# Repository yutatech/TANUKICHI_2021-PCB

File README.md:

# TANUKICHI_2021-PCB
This PCB is developed for RoboCup Junior Soccer. The robot has competed as "CAIO Tezukayama" in 2019 and "Leopard" in 2021.

## Related Web sites
- [Yuta's Blog](http://yuta.techblog.jp)
- [ Yuta - YouTube Channel](https://www.youtube.com/@yuta9428)
- [ Yuta@ciao_yuta - Twitter](https://twitter.com/ciao_yuta)

## Related Repositories
- [yutatech/RoboCup2021](https://github.com/yutatech/RoboCup2021)
- [yutatech/TANUKICHI_2021-Software](https://github.com/yutatech/TANUKICHI_2021-Software)

## Related Resources
#### TDP
- [Leopard RoboCup 2021 Team Discription Paper](http://yuta.techblog.jp/RoboCupJapanTournament2021/Leopard%20RoboCup%202021%20Team%20Discription%20Paper.pdf)

#### Video
- [Video - Leopard (Soccer Open) - RoboCup 2021 WORLDWIDE](https://www.youtube.com/watch?v=Lgoi_pQrCUY)
	- [This video](https://www.youtube.com/watch?v=PFkYVE7N84A) and [this video](https://www.youtube.com/watch?v=1l03lD6fXiQ) are also the same. Uploaded from TokyoTech.

## Awards
- ロボカップジュニア日本大会2021オンライン (RoboCup Junior Japan Tournament 2021 Online)
	- サッカーオープン 優勝 (SoccerOpen 1st Place)
	- ベストプレゼンビデオ賞 (Best Presentation Video Award)
	- ベストインタビュー賞 (Best Interview Award)
	- ベストビジュアルポスター賞 (Best Visual Poster Award)
- RoboCup 2021 WORLDWIDE
	- SoccerOpen Indvidual 1st Place
	- SoccerOpen SuperTeam 1st Place

## Environment
These files are edited with KiCAD 5.1.5

## PCB design files
- MAIN
	- This PCB is the main board of the robot. 
- MOTOR
	- This PCB drives 4 motors and 2 kickers. It is connected to MAIN with pin headers.
- LINE
	- This PCB includes 2 types of line sensor boards. The robot has two sensor boards of each type.
- TOP
	- This PCB distributes the wiring from MAIN to the devices mounted on top of the robot.
- BOTTOM
	- This PCB is connected to the line sensor board without using cables.
- BOOST V1
	- This PCB is a boost circuit for kickers. It outputs 60V. This version is installed to the robot because it is stable and works well.
- BOOST V2
	- This PCB is also a boost circuit for kickers. It outputs 150V. This version is an improvement on V1, but was not adopted because it would have caused noise in the surrounding circuit.
- ENCODER
	- This PCB is a magnetic pulse encoder board.
- PROTECTION
	- This PCB is Li-PO Battery protection circuit. The voltage of each cell is not monitored, so any imitation should be done at your own risk.

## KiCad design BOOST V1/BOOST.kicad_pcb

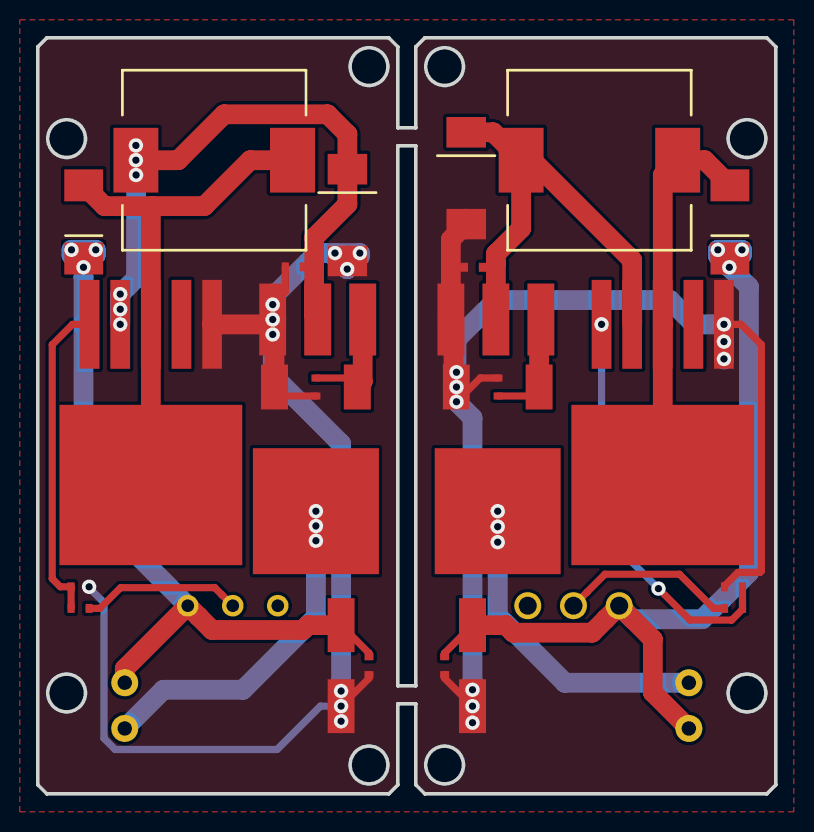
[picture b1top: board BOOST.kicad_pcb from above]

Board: 2 copper layers, 41.0 x 42.0 mm, 28 parts (0 on the bottom side), 15 nets.

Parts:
C1, C4: 100u; TANTALCAP-6032
C2, C3, C5, C6: 100n; 1005
D1, D2: D_Small; DO-214AC
J1, J4: INPUT; 3Pads
J2, J5: CAPACITOR; 2Pads
J3, J6: SOLENOID; Molex_2pin_angled
L1, L2: L; Inductor_10x10x3.8
Q1, Q2: Q_NMOS_GDS; TO-252
R1, R4: 2K; 1005
R2, R5: 470R; 1005
R3, R6: 1K; 1005
RV1, RV2: 20K; CONN_01x03
XL1, XL2: XL6019; TO263-5L

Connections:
GND: C1.2, C2.2, C3.2, C4.2, C5.2, C6.2, J1.1, J2.2, J4.1, J5.2, Q1.3, Q2.3, R2.2, R3.1, R5.2, R6.1, XL1.1, XL2.1
unnamed: C1.1, C2.1, J1.2, L1.2, XL1.4
unnamed: C3.1, D1.1, J2.1, J3.1, RV1.1
unnamed: C4.1, C5.1, J4.2, L2.2, XL2.4
unnamed: C6.1, D2.1, J5.1, J6.1, RV2.1
unnamed: D1.2, L1.1, XL1.3
unnamed: D2.2, L2.1, XL2.3
unnamed: J1.3, Q1.1, R3.2
unnamed: J3.2, Q1.2
unnamed: J4.3, Q2.1, R6.2
unnamed: J6.2, Q2.2
unnamed: R1.1, RV1.2
unnamed: R1.2, R2.1, XL1.5
unnamed: R4.1, RV2.2
unnamed: R4.2, R5.1, XL2.5

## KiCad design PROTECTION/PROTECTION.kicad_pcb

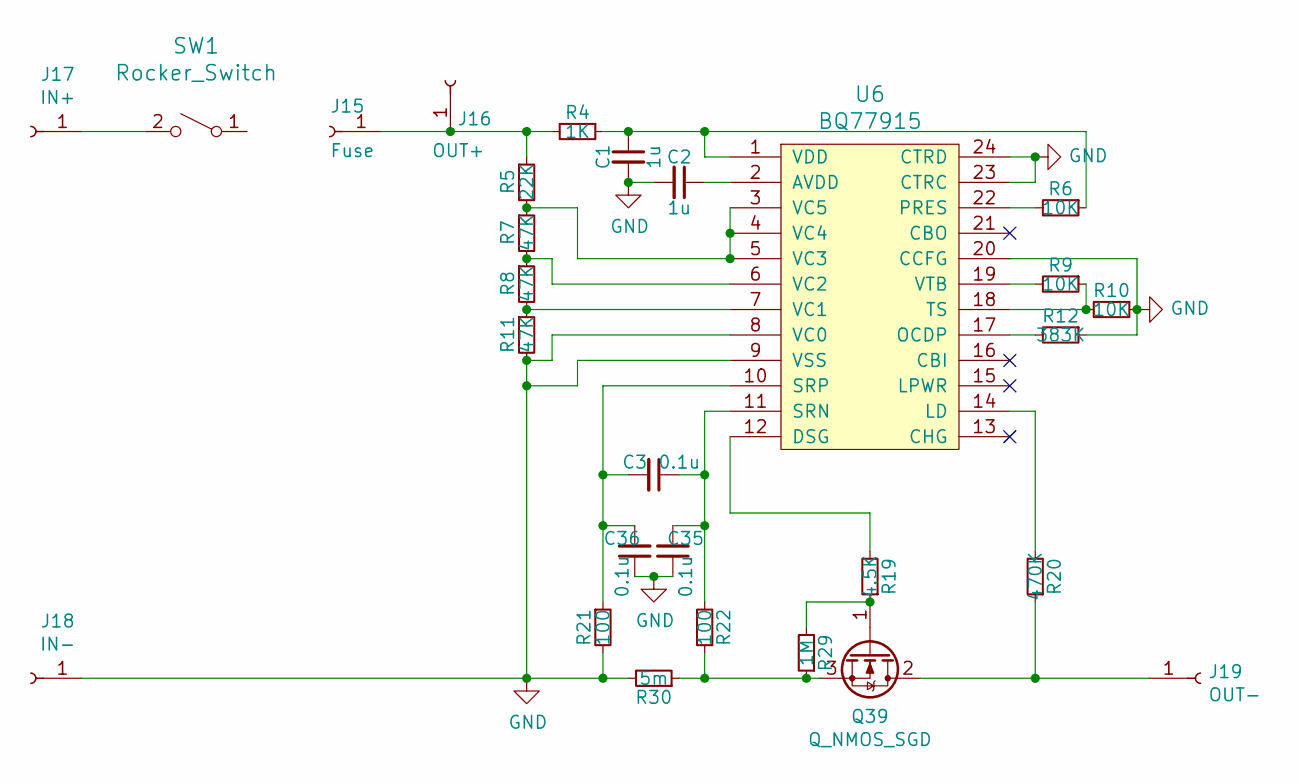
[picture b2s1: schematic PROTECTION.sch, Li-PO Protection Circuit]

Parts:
C1, C2: 1u; 1005
C3, C35, C36: 0.1u; 1005
J15: Fuse; 1PIN
J16: OUT+; 1PIN
J17: IN+; 1PIN
J18: IN-; 1PIN
J19: OUT-; 1PIN
Q39: Q_NMOS_SGD; TO-252; Part # DMTH6005LK3-13
R4: 1K; 1005
R5: 22K; 1005
R6, R9, R10: 10K; 1005
R7, R8, R11: 47K; 1005
R12: 383K; 1005
R19: 4.5K; 1005
R20: 470K; 1005
R21, R22: 100; 1005
R29: 1M; 1005
R30: 5m; 6432; Part # PCS2512FR0050ET
SW1: Rocker_Switch; 2Pads; Part # DS-850K-S-LG-K
U6: BQ77915; TSSOP-24

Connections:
GND: C1.2, C2.2, C35.1, C36.1, J18.1, R10.1, R11.2, R12.1, R21.2, R30.2, U6.8 (VC0), U6.9 (VSS), U6.20 (CCFG), U6.23 (CTRC), U6.24 (CTRD)
unnamed: C1.1, R4.1, R6.1, U6.1 (VDD)
unnamed: C2.1, U6.2 (AVDD)
unnamed: C3.1, C35.2, R22.2, U6.11 (SRN)
unnamed: C3.2, C36.2, R21.1, U6.10 (SRP)
unnamed: J15.1, J16.1, R4.2, R5.1
unnamed: J17.1, SW1.2 (B)
unnamed: J19.1, Q39.2 (D), R20.1
unnamed: Q39.1 (G), R19.1, R29.2
unnamed: Q39.3 (S), R22.1, R29.1, R30.1
unnamed: R5.2, R7.1, U6.3 (VC5), U6.4 (VC4), U6.5 (VC3)
unnamed: R6.2, U6.22 (PRES)
unnamed: R7.2, R8.1, U6.6 (VC2)
unnamed: R9.2, U6.19 (VTB)
unnamed: R9.1, R10.2, U6.18 (TS)
unnamed: R8.2, R11.1, U6.7 (VC1)
unnamed: R12.2, U6.17 (OCDP)
unnamed: R19.2, U6.12 (DSG)
unnamed: R20.2, U6.14 (LD)

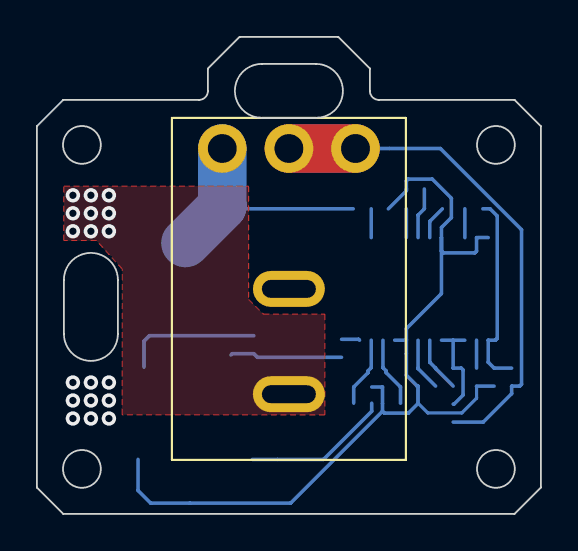
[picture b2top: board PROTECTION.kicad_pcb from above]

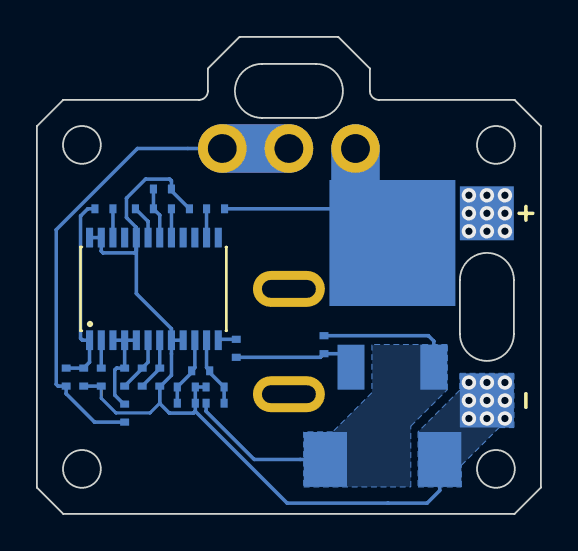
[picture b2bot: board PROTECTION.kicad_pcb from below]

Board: 2 copper layers, 28.0 x 26.5 mm, 28 parts (24 on the bottom side), 19 nets.

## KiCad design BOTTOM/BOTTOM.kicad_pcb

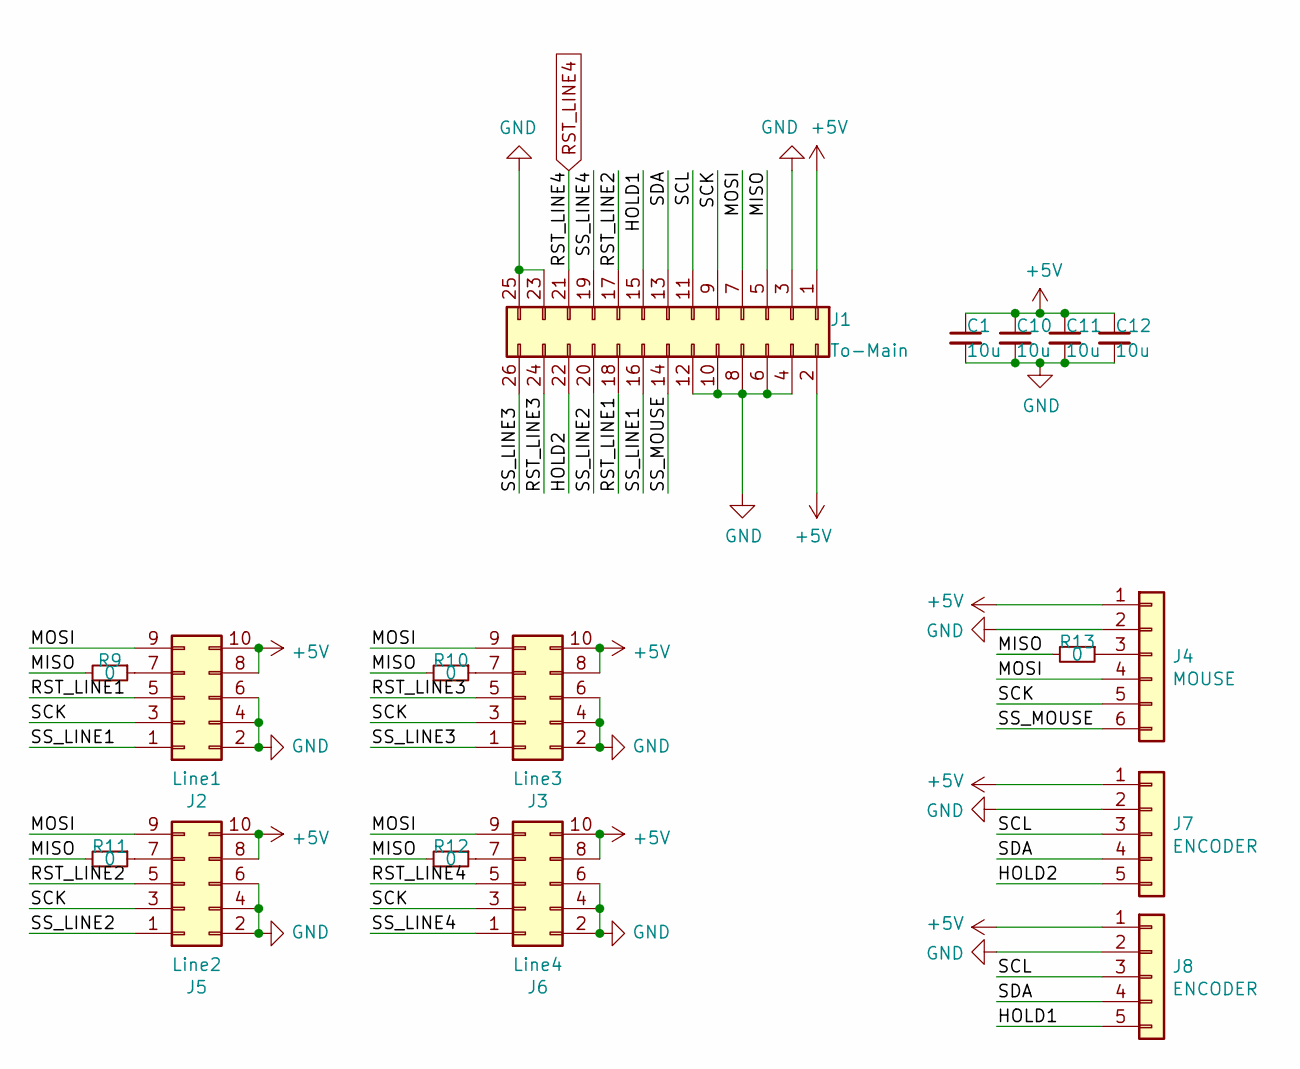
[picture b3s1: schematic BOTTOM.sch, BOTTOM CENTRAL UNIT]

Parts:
C1, C10, C11, C12: 10u; 2012
J1: To-Main; IDC_Header_Straight_26pins_P1.27mm; Part # 3220-26-0100-00
J2: Line1; CONN_SPRING_02x05_PADS
J3: Line3; CONN_SPRING_02x05_PADS
J4: MOUSE; CONN_01x06
J5: Line2; CONN_SPRING_02x05_PADS
J6: Line4; CONN_SPRING_02x05_PADS
J7, J8: ENCODER; CONN_01x05
R9, R10, R11, R12, R13: 0; 1005

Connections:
+5V: C1.1, C10.1, C11.1, C12.1, J1.1, J1.2, J2.8, J2.10, J3.8, J3.10, J4.1, J5.8, J5.10, J6.8, J6.10, J7.1, J8.1
/HOLD1: J1.15, J8.5
/HOLD2: J1.22, J7.5
/MISO: J1.5, R9.2, R10.2, R11.2, R12.2, R13.2
/MOSI: J1.7, J2.9, J3.9, J4.4, J5.9, J6.9
/RST_LINE1: J1.18, J2.5
/RST_LINE2: J1.17, J5.5
/RST_LINE3: J1.24, J3.5
/SCK: J1.9, J2.3, J3.3, J4.5, J5.3, J6.3
/SCL: J1.11, J7.3, J8.3
/SDA: J1.13, J7.4, J8.4
/SS_LINE1: J1.16, J2.1
/SS_LINE2: J1.20, J5.1
/SS_LINE3: J1.26, J3.1
/SS_LINE4: J1.19, J6.1
/SS_MOUSE: J1.14, J4.6
GND: C1.2, C10.2, C11.2, C12.2, J1.3, J1.4, J1.6, J1.8, J1.10, J1.12, J1.23, J1.25, J2.2, J2.4, J2.6, J3.2, J3.4, J3.6, J4.2, J5.2, J5.4, J5.6, J6.2, J6.4, J6.6, J7.2, J8.2
unnamed: J2.7, R9.1
unnamed: J3.7, R10.1
unnamed: J4.3, R13.1
unnamed: J5.7, R11.1
unnamed: J6.7, R12.1
RST_LINE4: J1.21, J6.5

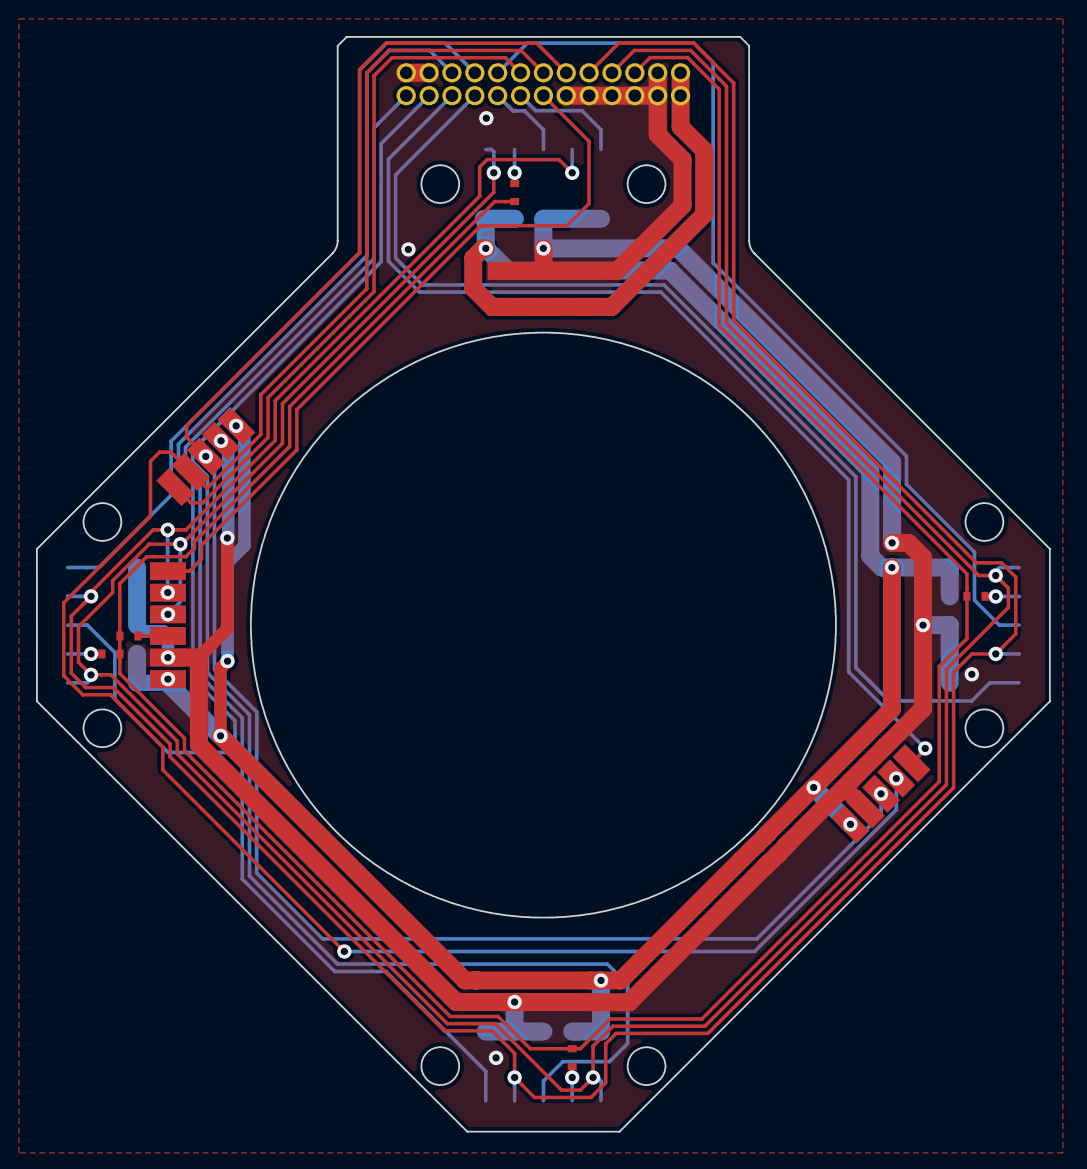
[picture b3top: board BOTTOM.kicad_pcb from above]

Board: 2 copper layers, 56.3 x 60.8 mm, 17 parts (0 on the bottom side), 23 nets.

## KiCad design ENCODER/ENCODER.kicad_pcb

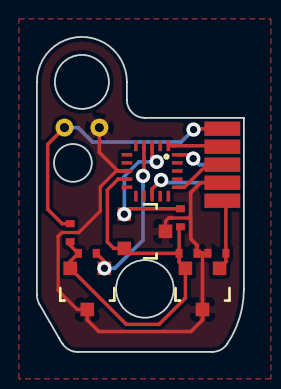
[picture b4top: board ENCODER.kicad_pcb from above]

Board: 2 copper layers, 11.5 x 17.5 mm, 12 parts (1 on the bottom side), 10 nets.

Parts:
C32, C33: 1u; 1005
J5: Conn_01x05; CONN_01x05
J11: Conn_01x02; 2Pads
Q24: Q_Photo_NPN; 2Pads
R28: 4.7K; 1005
R29, R30: 10K; 1005
U11: AP7333; Q_SOT-23
U12, U13: AH1751; Q_SOT-23
U14: ATtiny84A-MMH; QFN-20_P0.45

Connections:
+3V3: C33.2, R28.2, R29.1, R30.1, U11.2, U12.2, U13.2, U14.9
+5V: C32.1, J5.5, U11.1
/HOLD: J5.1, Q24.1, R28.1
/MISO: J11.2, U14.20
/RESET: J11.1, U14.13
/SCL\SCK: J5.2, U14.1
/SDA\MOSI: J5.3, U14.16
GND: C32.2, C33.1, J5.4, Q24.2, U11.3, U12.3, U13.3, U14.8
unnamed: R29.2, U12.1, U14.4
unnamed: R30.2, U13.1, U14.3

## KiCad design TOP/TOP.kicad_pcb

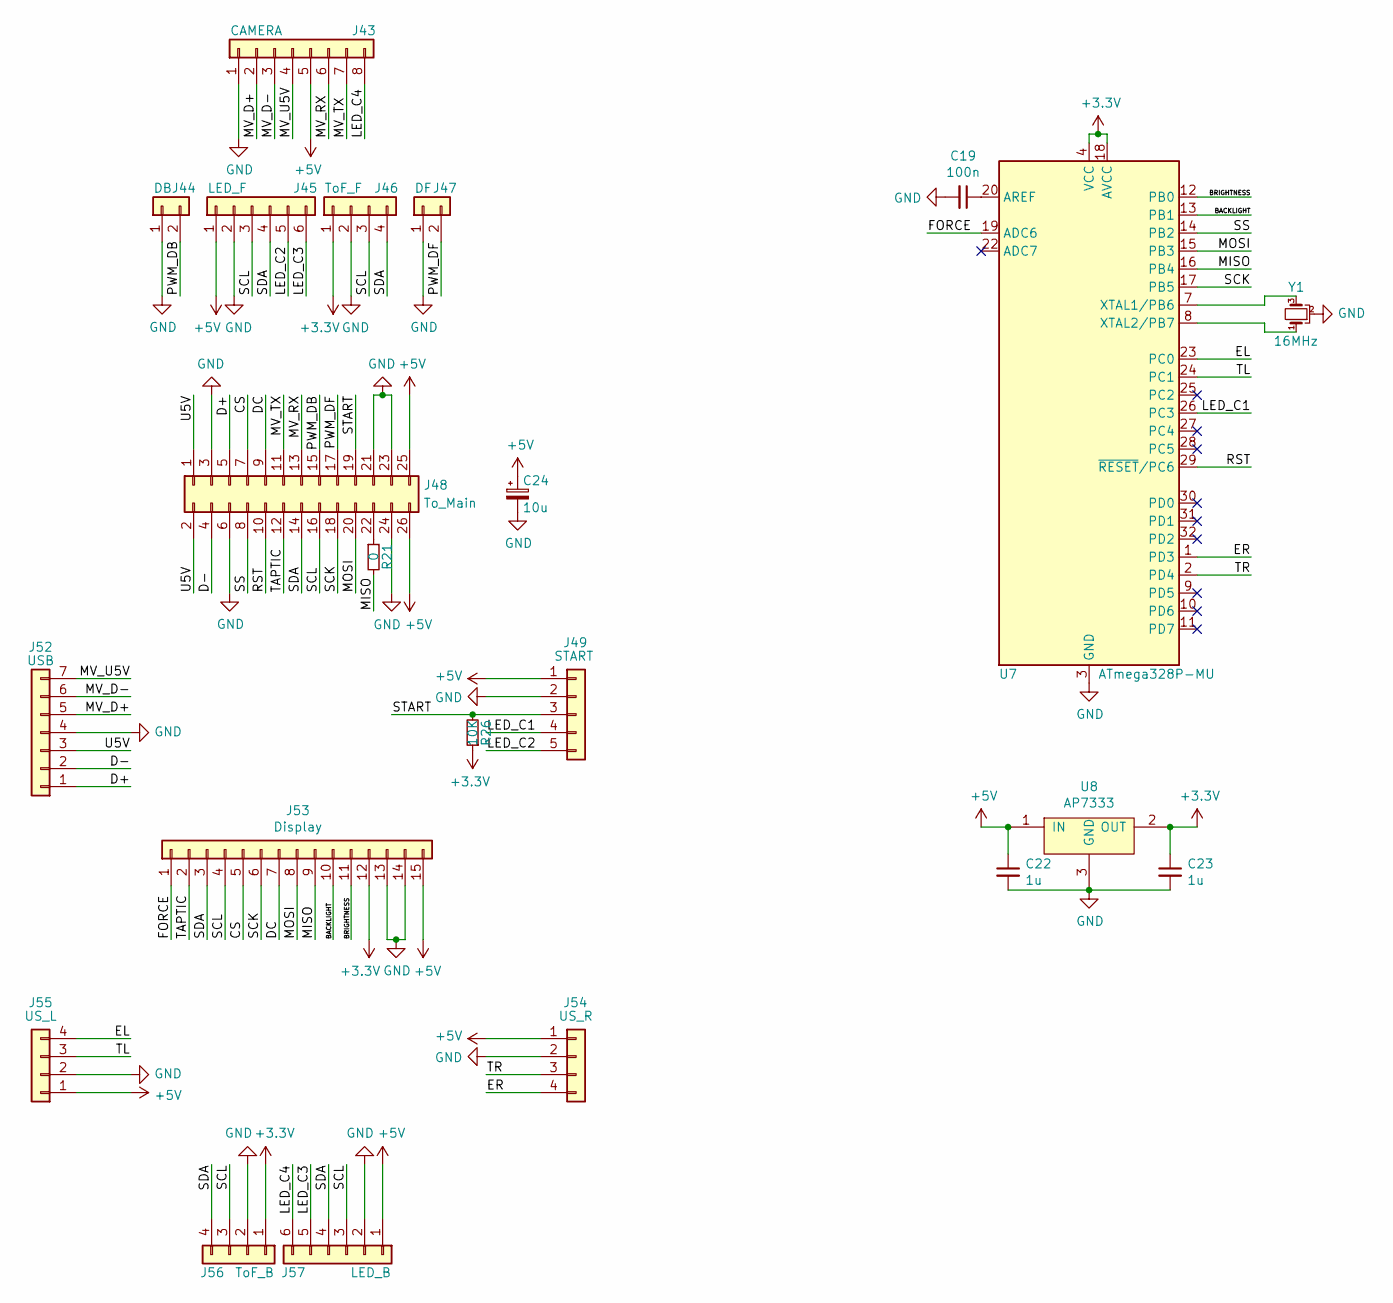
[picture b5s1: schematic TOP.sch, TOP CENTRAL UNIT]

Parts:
C19: 100n; 1005
C22, C23: 1u; 1005
C24: 10u; CAPACITOR_φ4
J43: CAMERA; PH-ST08
J44: DB; PH-ST02
J45: LED_F; PH-ST06
J46: ToF_F; PH-ST04
J47: DF; PH-ST02
J48: To_Main; IDC_Header_Straight_26pins_P1.27mm; Part # 3220-26-0100-00
J49: START; PH-ST05
J52: USB; PH-ST07
J53: Display; FFC 15P
J54: US_R; PH-ST04
J55: US_L; PH-ST04
J56: ToF_B; PH-ST04
J57: LED_B; PH-ST06
R21: 0; 1005
R26: 10K; 1005
U7: ATmega328P-MU; VQFN-32-5x5mm_P0.5mm
U8: AP7333; Q_SOT-23
Y1: 16MHz; CERALOCK; Part # CSTNE16M0V530000R0

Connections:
+3V3: C23.1, J46.1, J53.12, J56.1, R26.1, U7.4 (VCC), U7.6 (VCC), U7.18 (AVCC), U8.2 (OUT)
+5V: C22.1, C24.1, J43.5, J45.1, J48.25, J48.26, J49.1, J53.15, J54.1, J55.1, J57.1, U8.1 (IN)
/BACKLIGHT: J53.10, U7.13 (PB1)
/BRIGHTNESS: J53.11, U7.12 (PB0)
/CS: J48.7, J53.5
/D+: J48.5, J52.1
/D-: J48.4, J52.2
/DC: J48.9, J53.7
/EL: J55.4, U7.23 (PC0)
/ER: J54.4, U7.1 (PD3)
/FORCE: J53.1, U7.19 (ADC6)
/LED_C1: J49.4, U7.26 (PC3)
/LED_C2: J45.5, J49.5
/LED_C3: J45.6, J57.5
/LED_C4: J43.8, J57.6
/MISO: J53.9, R21.2, U7.16 (PB4)
/MOSI: J48.20, J53.8, U7.15 (PB3)
/MV_D+: J43.2, J52.5
/MV_D-: J43.3, J52.6
/MV_RX: J43.6, J48.13
/MV_TX: J43.7, J48.11
/MV_U5V: J43.4, J52.7
/PWM_DB: J44.2, J48.15
/PWM_DF: J47.2, J48.17
/RST: J48.10, U7.29 (~RESET~/PC6)
/SCK: J48.18, J53.6, U7.17 (PB5)
/SCL: J45.3, J46.3, J48.16, J53.4, J56.3, J57.3
/SDA: J45.4, J46.4, J48.14, J53.3, J56.4, J57.4
/SS: J48.8, U7.14 (PB2)
/START: J48.19, J49.3, R26.2
/TAPTIC: J48.12, J53.2
/TL: J55.3, U7.24 (PC1)
/TR: J54.3, U7.2 (PD4)
/U5V: J48.1, J48.2, J52.3
GND: C19.2, C22.2, C23.2, C24.2, J43.1, J44.1, J45.2, J46.2, J47.1, J48.3, J48.6, J48.21, J48.23, J48.24, J49.2, J52.4, J53.13, J53.14, J54.2, J55.2, J56.2, J57.2, U7.3 (GND), U7.5 (GND), U7.21 (GND), U7.33 (GND), U8.3 (GND), Y1.2
unnamed: C19.1, U7.20 (AREF)
unnamed: J48.22, R21.1
unnamed: U7.7 (XTAL1/PB6), Y1.3
unnamed: U7.8 (XTAL2/PB7), Y1.1

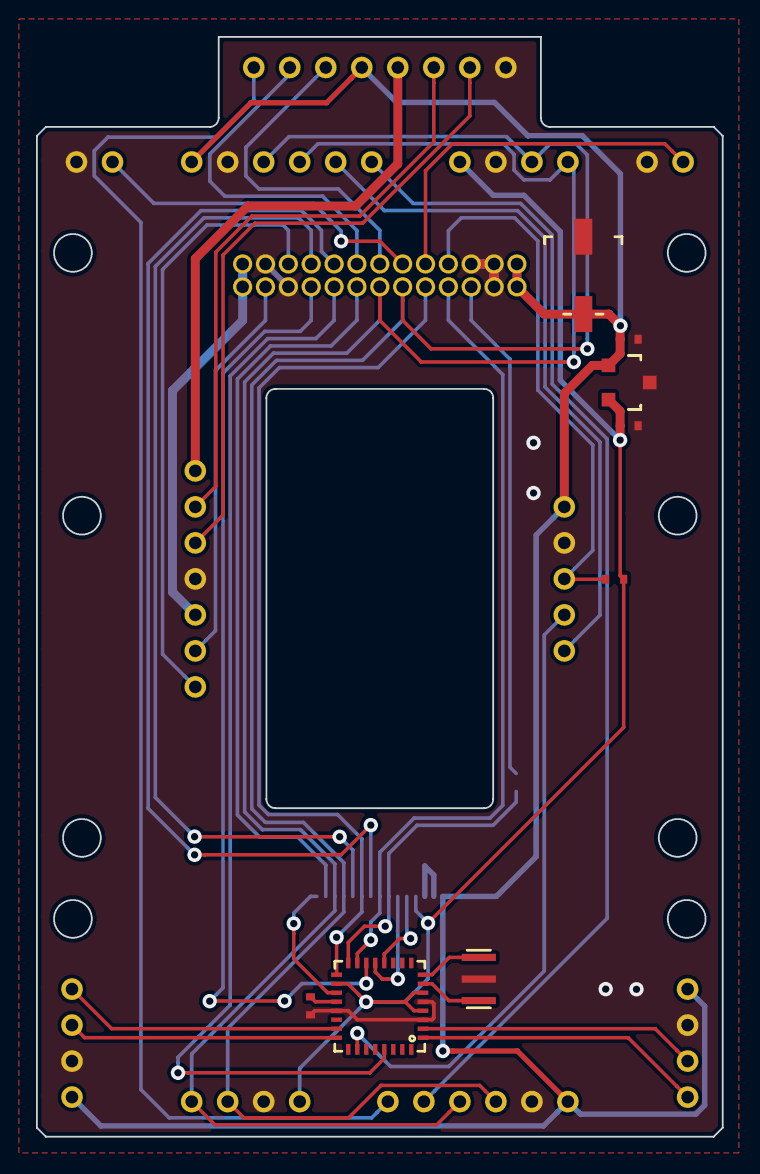
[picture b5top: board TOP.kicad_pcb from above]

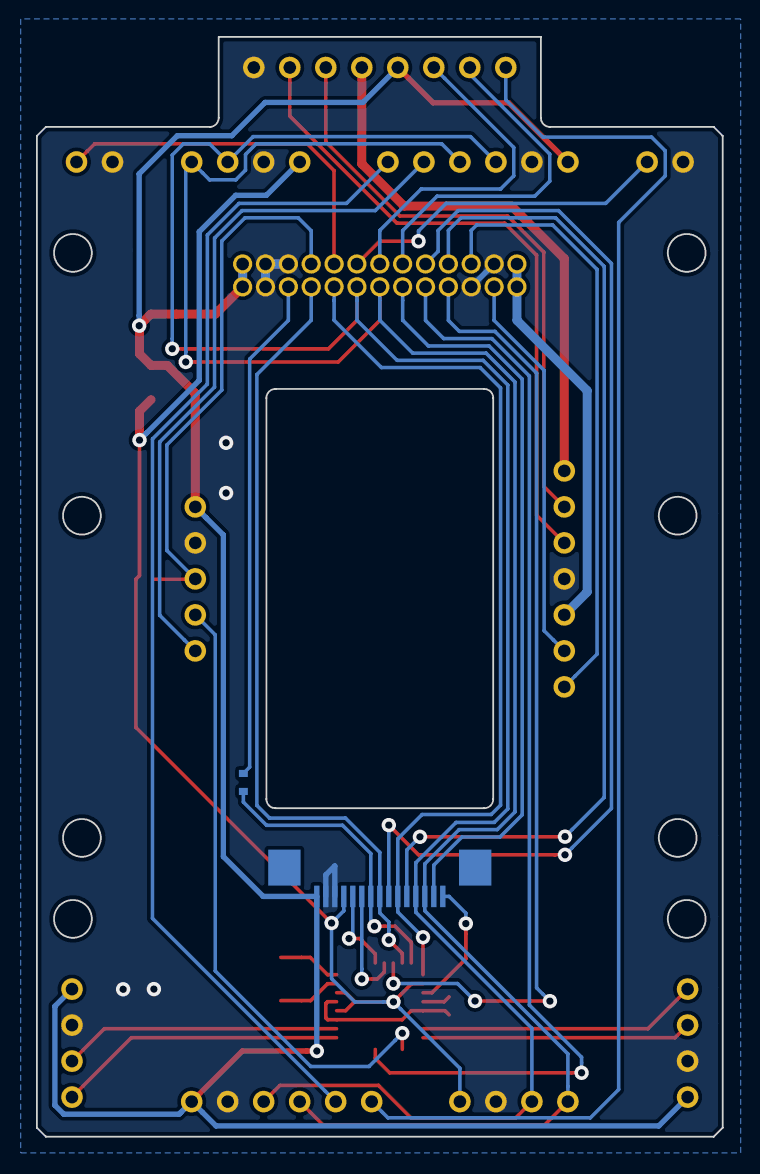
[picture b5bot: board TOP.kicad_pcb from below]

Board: 2 copper layers, 38.1 x 61.1 mm, 22 parts (13 on the bottom side), 39 nets.

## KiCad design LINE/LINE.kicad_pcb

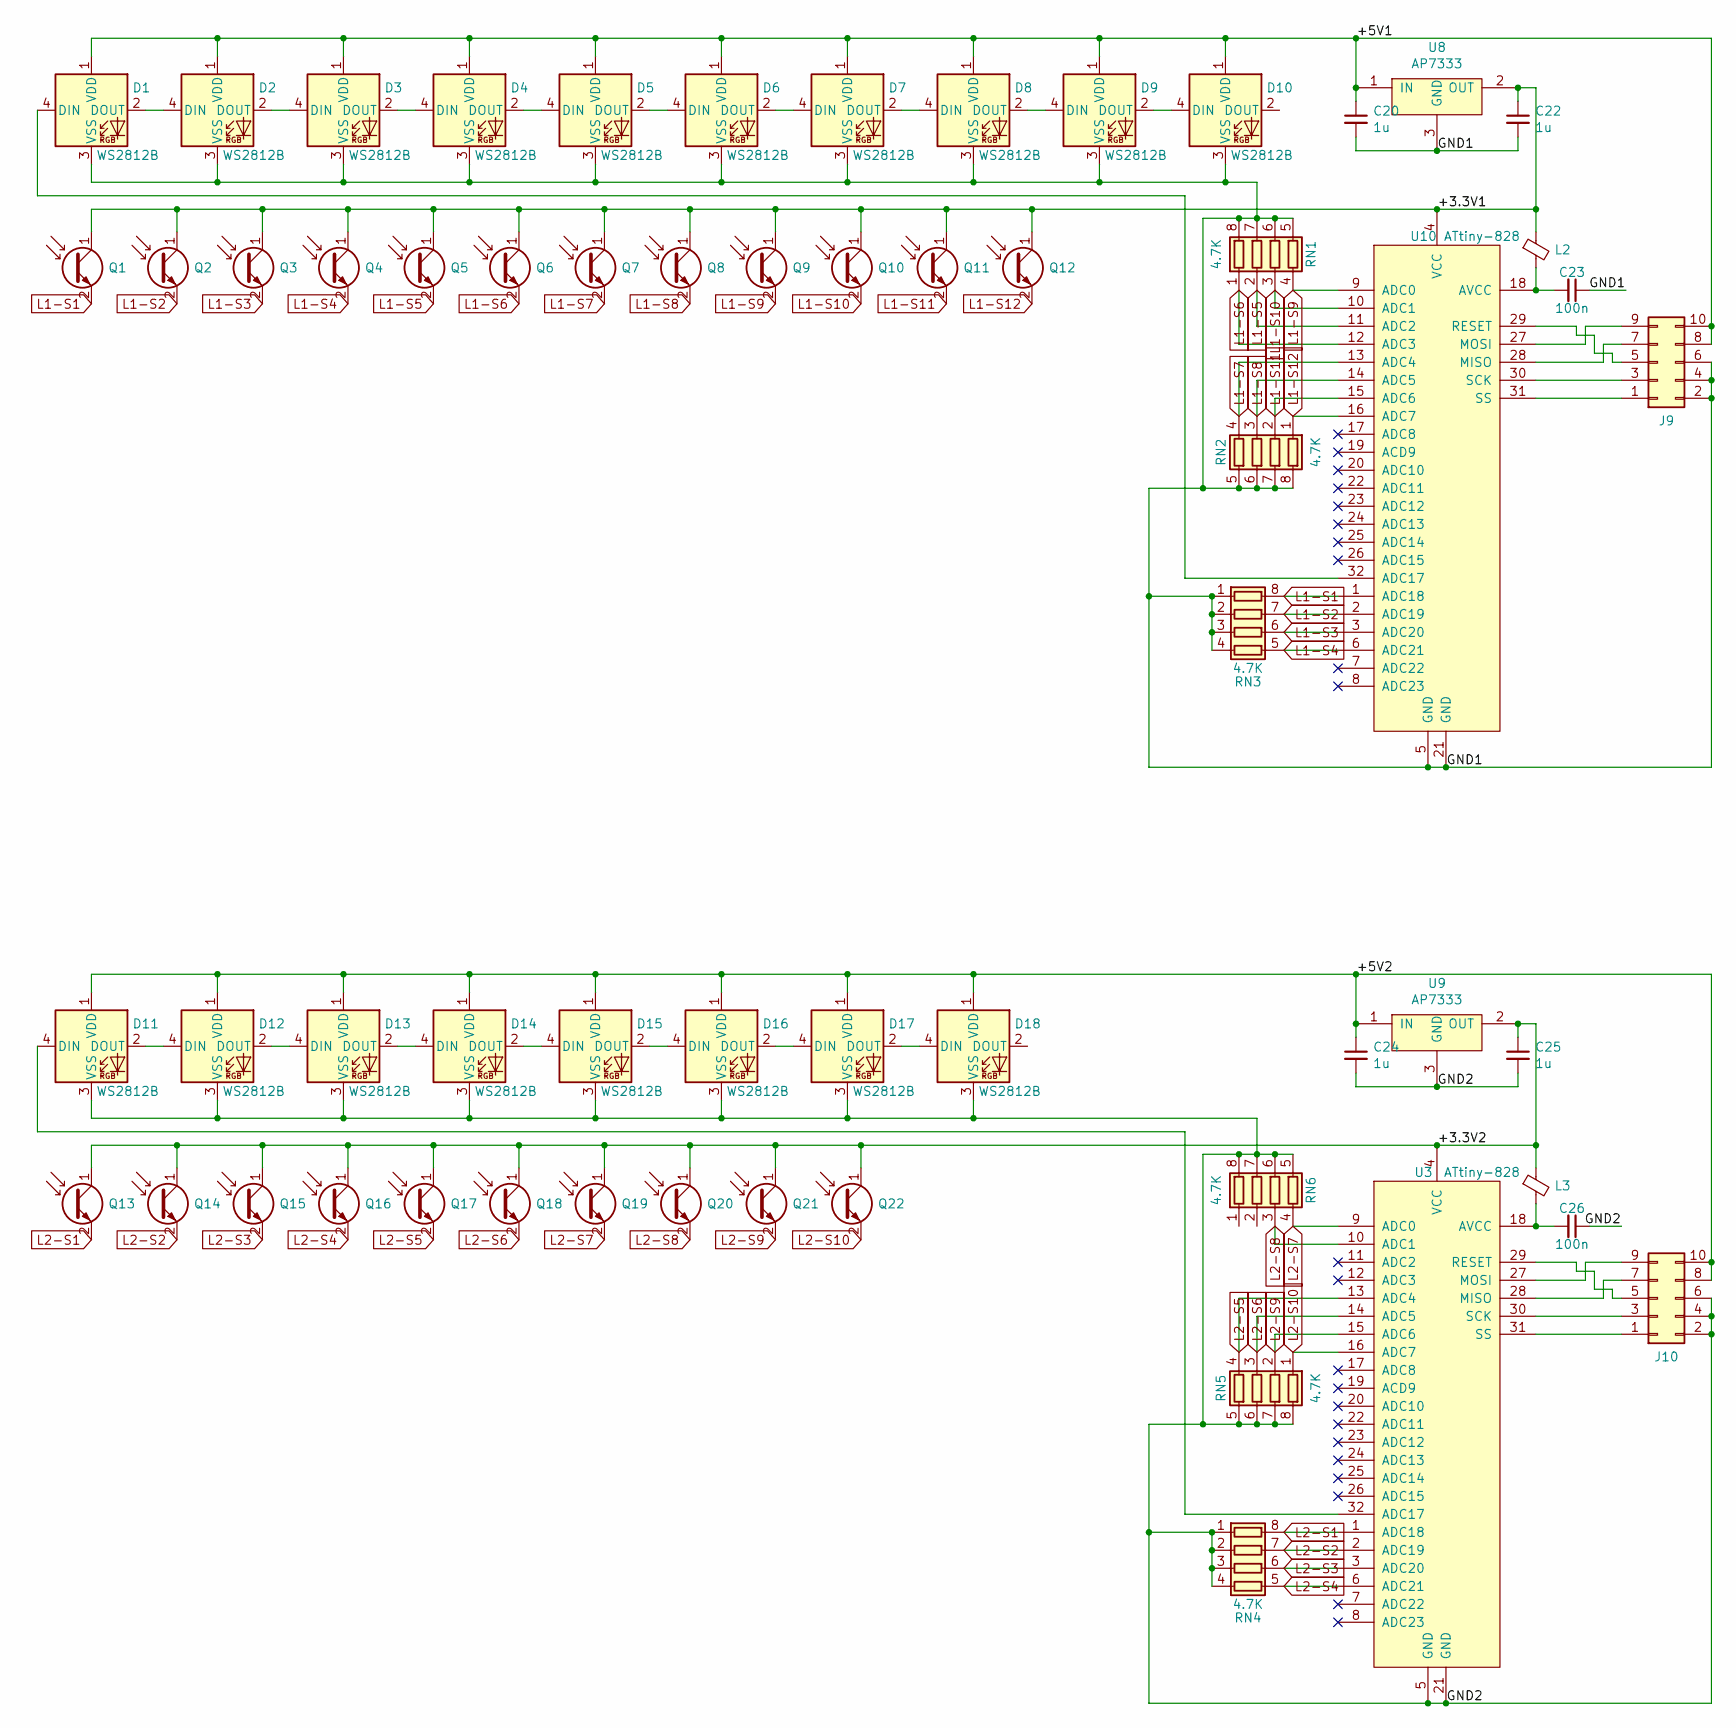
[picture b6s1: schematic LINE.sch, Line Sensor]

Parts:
C20, C22, C24, C25: 1u; 2012
C23, C26: 100n; 1005
D1, D2, D3, D4, D5, D6, D7, D8, D9, D10, D11, D12, D13, D14, D15, D16, D17, D18: WS2812B
J9, J10: Conn_02x05_Odd_Even; CONN_SPRING_02x05; Part # A120577CT-ND
L2, L3: Ferrite_Bead_Small; 1608
Q1, Q2, Q3, Q4, Q6, Q7, Q8, Q9, Q10, Q11, Q12, Q13, Q14, Q15, Q16, Q17, Q18, Q19, Q20, Q21, Q22: Q_Photo_NPN; PS1101W; Part # PS1101W
Q5: Q_Photo_NPN; PS1101W; PArt # PS1101W
RN1, RN2, RN3, RN4, RN5, RN6: 4.7K; 4RES_ARRAY_SMALL; Part # EXB-28V472JX
U3, U10: ATtiny-828; VQFN-32-5x5mm_P0.5mm
U8, U9: AP7333; Q_SOT-23

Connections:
/+3.3V1: C22.1, L2.1, Q1.1 (C), Q2.1 (C), Q3.1 (C), Q4.1 (C), Q5.1 (C), Q6.1 (C), Q7.1 (C), Q8.1 (C), Q9.1 (C), Q10.1 (C), Q11.1 (C), Q12.1 (C), U8.2 (OUT), U10.4 (VCC)
/+3.3V2: C25.1, L3.1, Q13.1 (C), Q14.1 (C), Q15.1 (C), Q16.1 (C), Q17.1 (C), Q18.1 (C), Q19.1 (C), Q20.1 (C), Q21.1 (C), Q22.1 (C), U3.4 (VCC), U9.2 (OUT)
/+5V1: C20.1, D1.1 (VDD), D2.1 (VDD), D3.1 (VDD), D4.1 (VDD), D5.1 (VDD), D6.1 (VDD), D7.1 (VDD), D8.1 (VDD), D9.1 (VDD), D10.1 (VDD), J9.8, J9.10, U8.1 (IN)
/+5V2: C24.1, D11.1 (VDD), D12.1 (VDD), D13.1 (VDD), D14.1 (VDD), D15.1 (VDD), D16.1 (VDD), D17.1 (VDD), D18.1 (VDD), J10.8, J10.10, U9.1 (IN)
/GND1: C20.2, C22.2, C23.1, D1.3 (VSS), D2.3 (VSS), D3.3 (VSS), D4.3 (VSS), D5.3 (VSS), D6.3 (VSS), D7.3 (VSS), D8.3 (VSS), D9.3 (VSS), D10.3 (VSS), J9.2, J9.4, J9.6, RN1.5 (R4.2), RN1.6 (R3.2), RN1.7 (R2.2), RN1.8 (R1.2), RN2.5 (R4.2), RN2.6 (R3.2), RN2.7 (R2.2), RN2.8 (R1.2), RN3.1 (R1.1), RN3.2 (R2.1), RN3.3 (R3.1), RN3.4 (R4.1), U8.3 (GND), U10.5 (GND), U10.21 (GND)
/GND2: C24.2, C25.2, C26.1, D11.3 (VSS), D12.3 (VSS), D13.3 (VSS), D14.3 (VSS), D15.3 (VSS), D16.3 (VSS), D17.3 (VSS), D18.3 (VSS), J10.2, J10.4, J10.6, RN4.1 (R1.1), RN4.2 (R2.1), RN4.3 (R3.1), RN4.4 (R4.1), RN5.5 (R4.2), RN5.6 (R3.2), RN5.7 (R2.2), RN5.8 (R1.2), RN6.5 (R4.2), RN6.6 (R3.2), RN6.7 (R2.2), RN6.8 (R1.2), U3.5 (GND), U3.21 (GND), U9.3 (GND)
L1-S1: Q1.2 (E), RN3.8 (R1.2), U10.1 (ADC18)
L1-S2: Q2.2 (E), RN3.7 (R2.2), U10.2 (ADC19)
L1-S3: Q3.2 (E), RN3.6 (R3.2), U10.3 (ADC20)
L1-S4: Q4.2 (E), RN3.5 (R4.2), U10.6 (ADC21)
L1-S5: Q5.2 (E), RN1.2 (R2.1), U10.11 (ADC2)
L1-S6: Q6.2 (E), RN1.1 (R1.1), U10.12 (ADC3)
L1-S7: Q7.2 (E), RN2.4 (R4.1), U10.13 (ADC4)
L1-S8: Q8.2 (E), RN2.3 (R3.1), U10.14 (ADC5)
L1-S9: Q9.2 (E), RN1.4 (R4.1), U10.9 (ADC0)
L1-S10: Q10.2 (E), RN1.3 (R3.1), U10.10 (ADC1)
L1-S11: Q11.2 (E), RN2.2 (R2.1), U10.15 (ADC6)
L1-S12: Q12.2 (E), RN2.1 (R1.1), U10.16 (ADC7)
L2-S1: Q13.2 (E), RN4.8 (R1.2), U3.1 (ADC18)
L2-S2: Q14.2 (E), RN4.7 (R2.2), U3.2 (ADC19)
L2-S3: Q15.2 (E), RN4.6 (R3.2), U3.3 (ADC20)
L2-S4: Q16.2 (E), RN4.5 (R4.2), U3.6 (ADC21)
L2-S5: Q17.2 (E), RN5.4 (R4.1), U3.13 (ADC4)
L2-S6: Q18.2 (E), RN5.3 (R3.1), U3.14 (ADC5)
L2-S7: Q19.2 (E), RN6.4 (R4.1), U3.9 (ADC0)
L2-S8: Q20.2 (E), RN6.3 (R3.1), U3.10 (ADC1)
L2-S9: Q21.2 (E), RN5.2 (R2.1), U3.15 (ADC6)
L2-S10: Q22.2 (E), RN5.1 (R1.1), U3.16 (ADC7)
unnamed: C23.2, L2.2, U10.18 (AVCC)
unnamed: C26.2, L3.2, U3.18 (AVCC)
unnamed: D1.2 (DOUT), D2.4 (DIN)
unnamed: D1.4 (DIN), U10.32 (ADC17)
unnamed: D2.2 (DOUT), D3.4 (DIN)
unnamed: D3.2 (DOUT), D4.4 (DIN)
unnamed: D4.2 (DOUT), D5.4 (DIN)
unnamed: D5.2 (DOUT), D6.4 (DIN)
unnamed: D6.2 (DOUT), D7.4 (DIN)
unnamed: D7.2 (DOUT), D8.4 (DIN)
unnamed: D8.2 (DOUT), D9.4 (DIN)
unnamed: D9.2 (DOUT), D10.4 (DIN)
unnamed: D11.2 (DOUT), D12.4 (DIN)
unnamed: D11.4 (DIN), U3.32 (ADC17)
unnamed: D12.2 (DOUT), D13.4 (DIN)
unnamed: D13.2 (DOUT), D14.4 (DIN)
unnamed: D14.2 (DOUT), D15.4 (DIN)
unnamed: D15.2 (DOUT), D16.4 (DIN)
unnamed: D16.2 (DOUT), D17.4 (DIN)
unnamed: D17.2 (DOUT), D18.4 (DIN)
unnamed: J9.1, U10.31 (SS)
unnamed: J9.3, U10.30 (SCK)
unnamed: J9.5, U10.29 (RESET)
unnamed: J9.7, U10.28 (MISO)
unnamed: J9.9, U10.27 (MOSI)
unnamed: J10.1, U3.31 (SS)
unnamed: J10.3, U3.30 (SCK)
unnamed: J10.5, U3.29 (RESET)
unnamed: J10.7, U3.28 (MISO)
unnamed: J10.9, U3.27 (MOSI)

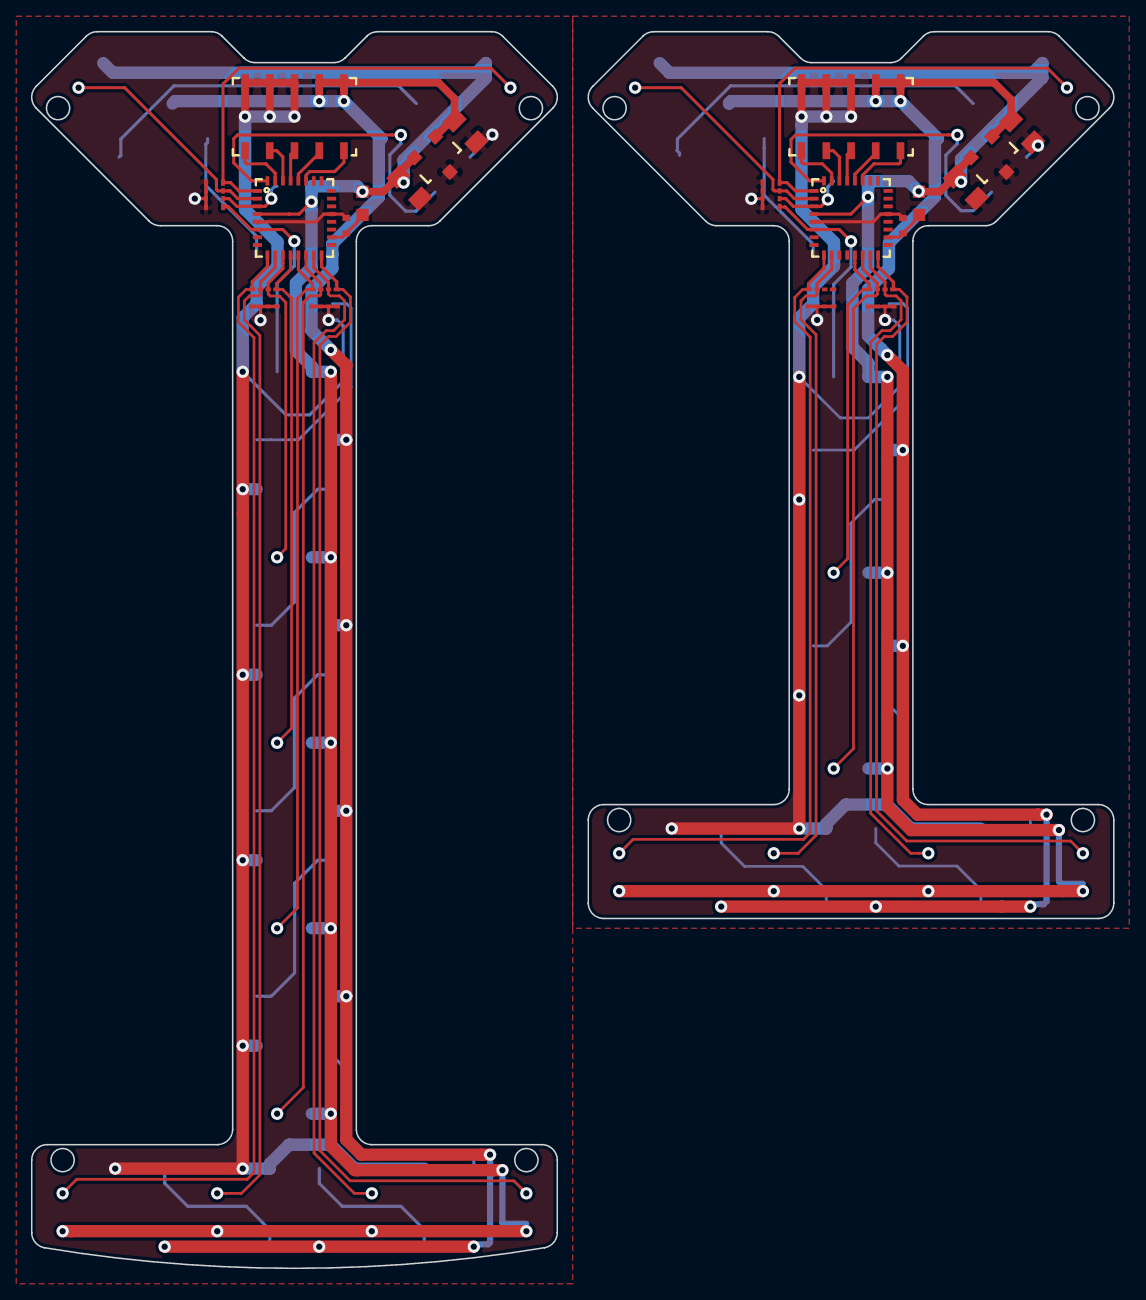
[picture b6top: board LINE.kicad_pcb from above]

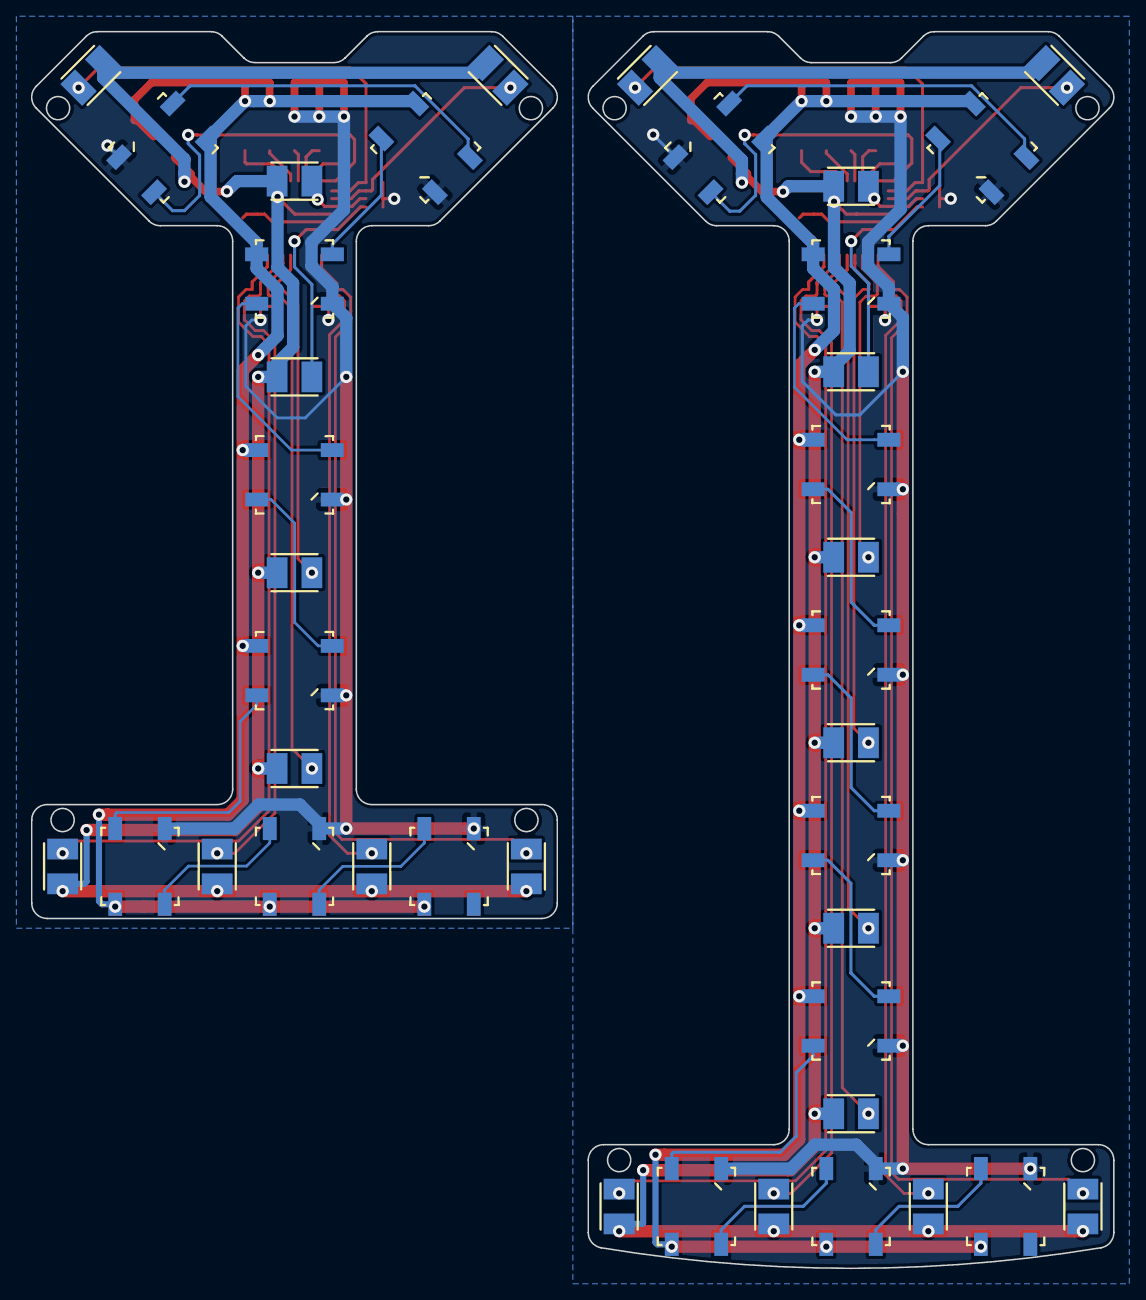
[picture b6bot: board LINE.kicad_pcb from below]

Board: 2 copper layers, 70.0 x 80.0 mm, 60 parts (40 on the bottom side), 58 nets.
